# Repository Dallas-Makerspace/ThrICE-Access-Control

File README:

All schematics and circuit board designs are licensed under a Creative Commons Attribution-ShareAlike 3.0 Unported License.

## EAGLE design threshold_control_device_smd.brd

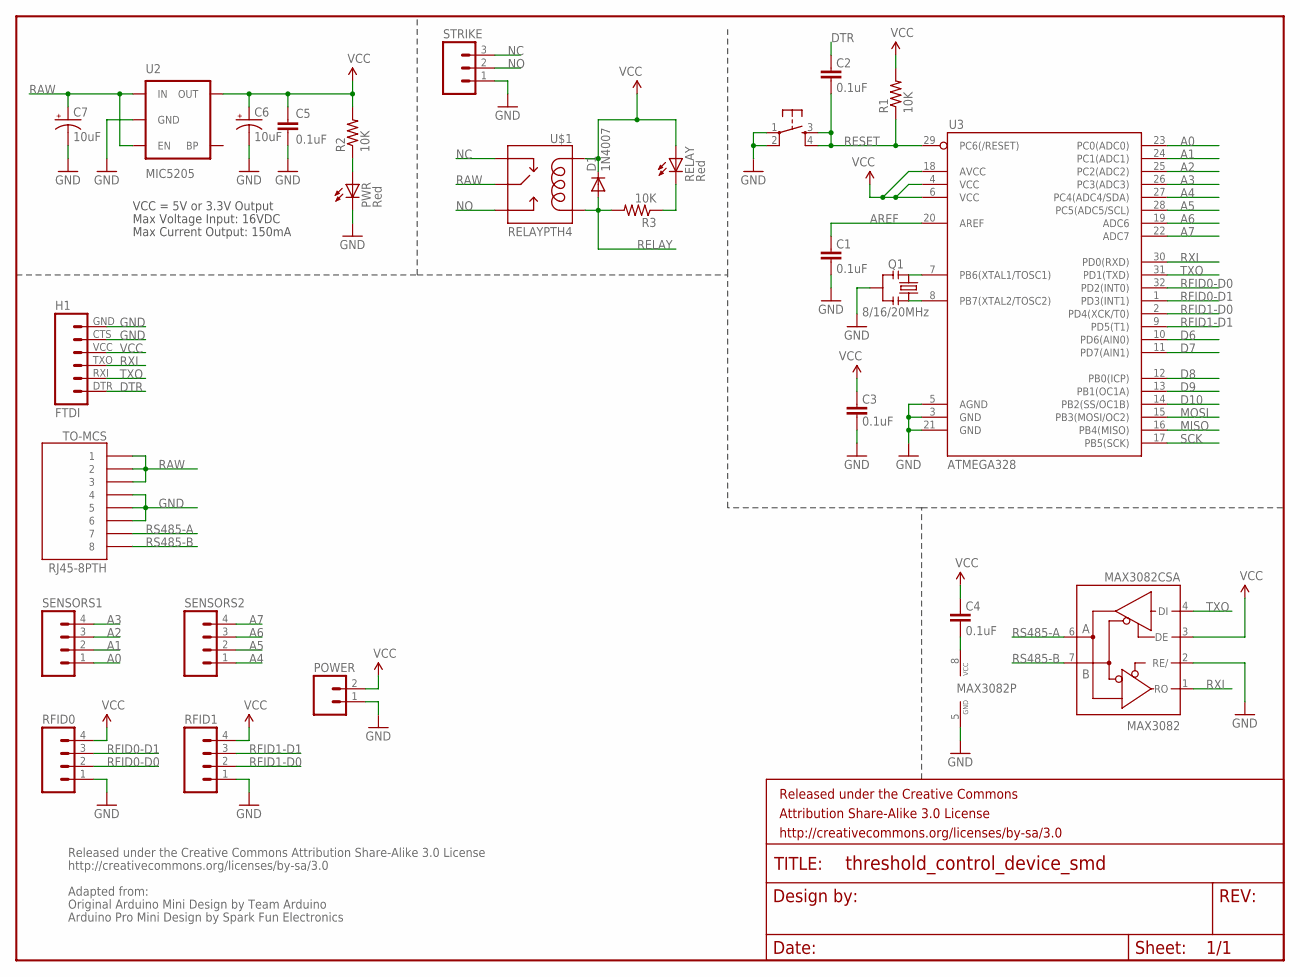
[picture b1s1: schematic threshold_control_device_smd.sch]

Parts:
C1, C2, C3, C4, C5: 0.1uF; 0402-CAP
C6, C7: 10uF; EIA3216
D1: 1N4007; SMA-DIODE
FRAME1: FRAME-LETTER; CREATIVE_COMMONS
H1: FTDI; FTDI_BASIC
MAX3082: MAX3082CSA; SO08
POWER: M023.5MM; SCREWTERMINAL-3.5MM-2
PWR: Red; LED-0603
Q1: 8/16/20MHz; RESONATOR-SMD
R1, R2, R3: 10K; 0402-RES
RELAY: Red; LED-0603
RESET: Reset; TACTILE_SWITCH_SMD
RFID0, RFID1: M04SCREW; SCREWTERMINAL-3.5MM-4
SENSORS1, SENSORS2: M04SCREW; SCREWTERMINAL-3.5MM-4
STRIKE: M03SCREW; SCREWTERMINAL-3.5MM-3
TO-MCS: RJ45-8PTH; RJ45-8
U2: MIC5205; SOT23-5
U3: ATMEGA328; TQFP32-08
U$1: RELAYPTH4; RELAY-JZC

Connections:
A0: SENSORS1.1, U3.23 (PC0(ADC0))
A1: SENSORS1.2, U3.24 (PC1(ADC1))
A2: SENSORS1.3, U3.25 (PC2(ADC2))
A3: SENSORS1.4, U3.26 (PC3(ADC3))
A4: SENSORS2.1, U3.27 (PC4(ADC4/SDA))
A5: SENSORS2.2, U3.28 (PC5(ADC5/SCL))
A6: SENSORS2.3, U3.19 (ADC6)
A7: SENSORS2.4, U3.22 (ADC7)
AREF: C1.2, U3.20 (AREF)
D6: U3.10 (PD6(AIN0))
D7: U3.11 (PD7(AIN1))
D8: U3.12 (PB0(ICP))
D9: U3.13 (PB1(OC1A))
D10: U3.14 (PB2(SS/OC1B))
DTR: C2.2, H1.DTR (1)
GND: C1.1, C3.1, C5.2, C6.C (-), C7.C (-), H1.CTS (5), H1.GND (6), MAX3082.2 (RE/), MAX3082.5 (GND), POWER.1, PWR.C, Q1.2, RESET.1, RESET.2, RFID0.1, RFID1.1, STRIKE.1, TO-MCS.4, TO-MCS.5, TO-MCS.6, U2.2 (GND), U3.3 (GND), U3.5 (AGND), U3.21 (GND)
MISO: U3.16 (PB4(MISO))
MOSI: U3.15 (PB3(MOSI/OC2))
unnamed: Q1.1, U3.8 (PB7(XTAL2/TOSC2))
unnamed: Q1.3, U3.7 (PB6(XTAL1/TOSC1))
unnamed: C4.1, MAX3082.8 (VCC)
unnamed: R3.1, RELAY.C
unnamed: PWR.A, R2.1
NC: STRIKE.3, U$1.2 (NC)
NO: STRIKE.2, U$1.3 (NO)
RAW: C7.A (+), TO-MCS.1, TO-MCS.2, TO-MCS.3, U2.1 (IN), U2.3 (EN), U$1.4 (MAIN)
RELAY: D1.A, R3.2, U$1.1 (COIL2)
RESET: C2.1, R1.1, RESET.3, RESET.4, U3.29 (PC6(/RESET))
RFID0-D0: RFID0.2, U3.32 (PD2(INT0))
RFID0-D1: RFID0.3, U3.1 (PD3(INT1))
RFID1-D0: RFID1.2, U3.2 (PD4(XCK/T0))
RFID1-D1: RFID1.3, U3.9 (PD5(T1))
RS485-A: MAX3082.6 (A), TO-MCS.7
RS485-B: MAX3082.7 (B), TO-MCS.8
RXI: H1.TXO (3), MAX3082.1 (RO), U3.30 (PD0(RXD))
SCK: U3.17 (PB5(SCK))
TXO: H1.RXI (2), MAX3082.4 (DI), U3.31 (PD1(TXD))
VCC: C3.2, C4.2, C5.1, C6.A (+), D1.C, H1.VCC (4), MAX3082.3 (DE), POWER.2, R1.2, R2.2, RELAY.A, RFID0.4, RFID1.4, U2.5 (OUT), U3.4 (VCC), U3.6 (VCC), U3.18 (AVCC), U$1.5 (COIL1)

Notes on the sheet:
Max Voltage Input: 16VDC
Max Current Output: 150mA
VCC = 5V or 3.3V Output
Released under the Creative Commons Attribution Share-Alike 3.0 License
http://creativecommons.org/licenses/by-sa/3.0
Original Arduino Mini Design by Team Arduino
Arduino Pro Mini Design by Spark Fun Electronics
Adapted from:

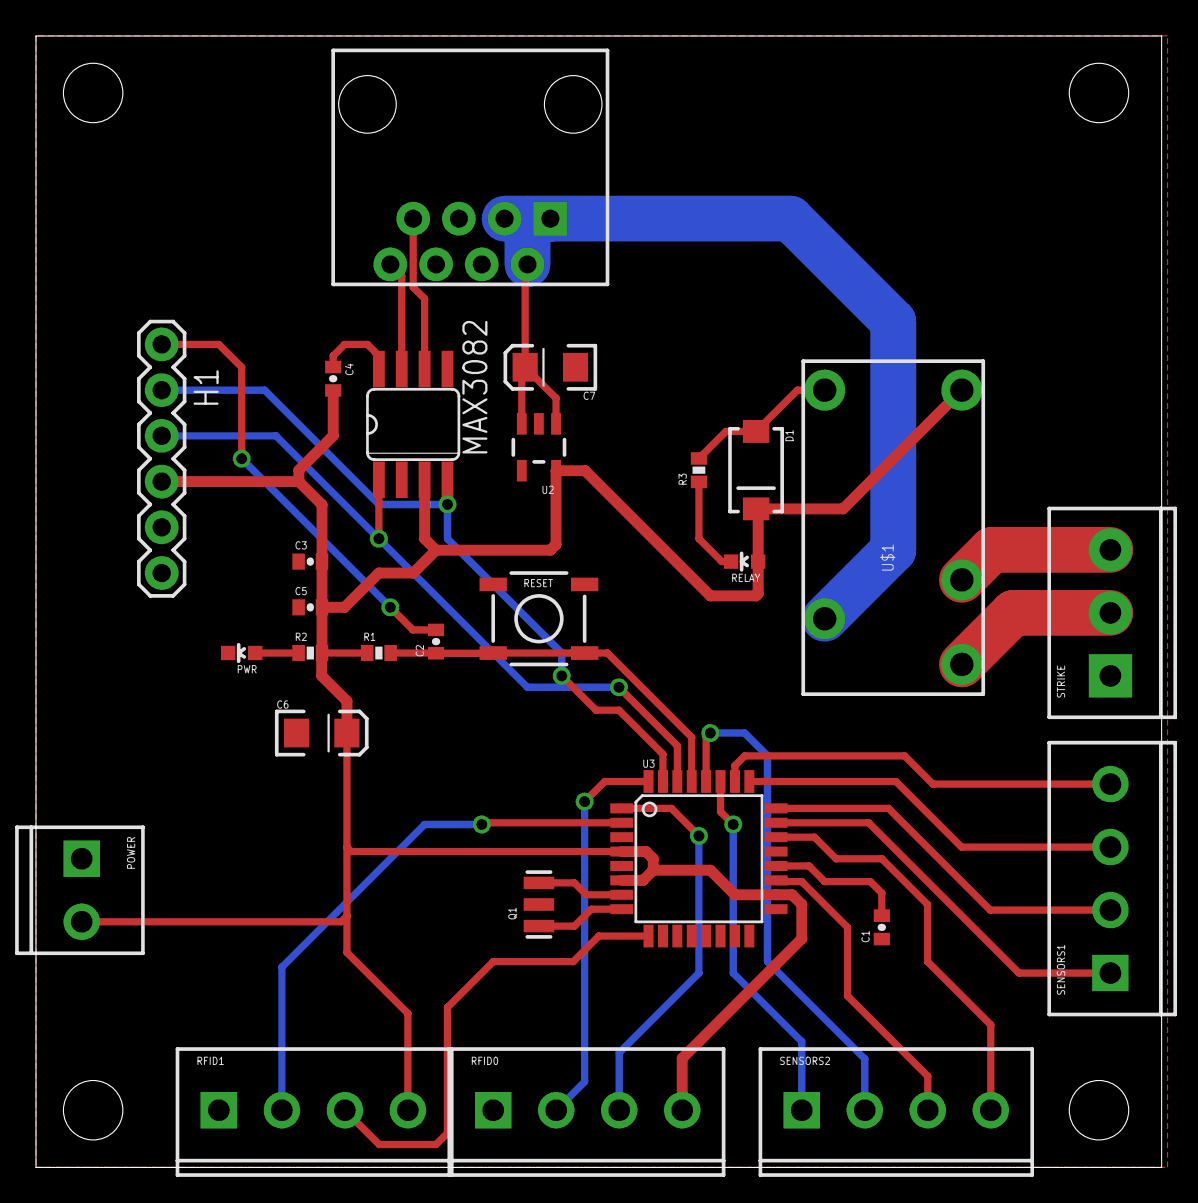
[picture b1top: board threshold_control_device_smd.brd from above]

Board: 2 copper layers, 62.5 x 62.9 mm, 32 parts (0 on the bottom side), 30 nets.

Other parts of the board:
U$2, U$3, U$4, U$5: STAND-OFF

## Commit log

2011-06-26 First commit, HIA schematic and board mostly done.
2011-06-26 Adding code directory.
2011-06-26 Removed reset switch, and ICSP header. Connected the Arduino to the buzzer. Added 5v for the motion detector. Redid the board layout, added 0.07" traces for the 12v strike.
2011-06-27 Removed files and added a .gitignore
2011-06-27 Minor route changes.
2011-06-27 Started work on MCA.
2011-06-27 Simplified the HIA some more. HIA can now use the ID-12 or Parallax's RFID reader. HIA board has been rearranged and a new board created for the ID-12.
2011-07-04 HIA mostly done, just need to tweak the routes for the keypad header. Started work on the MCA shield (master_control_shield).
2011-07-04 HIA complete, only a handful of traces remain on the bottom layer so it might be possible to make the board single layer (with the bottom being just ground.
2011-07-04 Added power supply circuitry, based on the designs from the open-access-control project. http://code.google.com/p/open-access-control/
2011-08-04 HIA is now single sided, so it should be easier to fab in house. You'll just need a 0 Ohm resistor.
2011-08-05 Still single sided for the HIA, but now you don't need to use a jumper (or 0 Ohm resistor).
2011-08-05 Minor tweaks.
2011-08-07 Renamed system components. HIA is now TCD (Threshold Control Device) and MCA is now MCS (Master Control System).
2011-08-07 Schematic for the MCS is mostly done. The board is too large for me to design it with the free version of Eagle, which will set things back a bit. Moved the power regulation off board to save space.
2011-08-10 Modified the TCD to fit the new design idea (all sensors polled via serial). I'll have to redo the board later so that the sensors are connected to the ADC.
2011-08-10 Basic idea I had for a TCD "filter" to protect the MCS from attack.
2011-08-10 Complete rework of the design to allow for expansion boards.
2011-08-11 More changes, renamed the shield to the mega_shield because the new version will work with a standard Arduino.
2011-08-11 Master Control Shield is basically done. It has 6 jumpers but it is technically single layer.
2011-08-11 MCS and MCS expansion are done, maybe.
2011-08-13 Added DMS logo to the boards.
2011-08-13 There's probably an award for people too stupid to use a transistor properly.
2011-08-13 Moved the ID-12 breakout to it's own file.
2011-08-13 Minor changes, mostly cosmetic.
2011-08-13 More minor tweaks.
2011-08-18 Started work on rs485 variant.
2011-08-18 RS485 variant completed, still needs to be tested.
2011-08-18 Moved RS232 variant to it's own folder.
2011-08-18 Minor tweaks to the RS485 variant.
2011-08-18 I'm not sure why git is saying the file was renamed (it wasn't). Just doing some more minor tweaks to make things look nice.
2011-08-18 Rounded corners, because it looks cool.
2011-08-18 Minor tweaks after running a design rule check.
2011-08-18 All 12v traces are now 86 mils for each relay (at least), 150 mils for the backbone link and 100 mils on the TCD.
2011-09-03 Modified MCS to use the TPIC6B595 power logic shift register, as the original shift register could not source enough current to activate the relays.
2011-09-03 Playing around with an SMD version of the TCD.
2011-09-10 MCS Expansion board needs to be redone due to the new shift register, and the change made to how the boards are inter-connected.
2011-09-19 MCS Expansion redone to use the Power Shift Register. ID-12 modified to have slightly larger traces, to make it easier to etch. TCD modified to have a resistor for each color on the RGB led. Power Co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
2011-09-19 Switched to a lower poly version of the logo.
2011-10-07 Minor tweaks for production.
2011-10-30 Minor cosmetic tweaks to the TCD.
2012-08-05 Scratch that, lets try this all over again...

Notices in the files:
parts and their libraries:
SparkFun-Aesthetics: Licensing: CC v3.0 Share-Alike You are welcome to use this library for commercial purposes.
